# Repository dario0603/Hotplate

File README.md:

# Hotplate

**An open-source hotplate project for electronics and PCB work.**

> **Work in Progress** — This project is currently under development. Hardware designs, PCB revisions, documentation, and other project files may change.

## Overview

Hotplate is a DIY electronics project focused on the design and development of a hotplate and its associated control electronics.

This repository is intended to collect the hardware designs, PCB documentation, and project resources as development progresses.

## PCB Designs

### Hotplate Resistor

The custom PCB designed for the hotplate heating element.

### Hotplate Control Board v1.1

The control electronics PCB, revision v1.1.

## Repository Structure

```text
Hotplate/
├── img/
│   ├── hotplate-control-board-v1.1.png
│   └── hotplate-resistor.png
├── Kicad/
│   ├── Control board/
│   │   ├── Control board v1.0/
│   │   ├── Control board v1.1/
│   │   └── Control board v1.2/
│   ├── Resistor 10x10/
│   └── Resistor 15x15/
├── Program/
│   ├── lib/
│   ├── Master/
│   ├── Master_prova/
│   ├── backup1/
│   └── backup 2/
├── Simulation and circuits/
└── README.md
```

This tree shows the main project directories. Individual KiCad libraries, 3D models, backup files, and simulation outputs are omitted for readability

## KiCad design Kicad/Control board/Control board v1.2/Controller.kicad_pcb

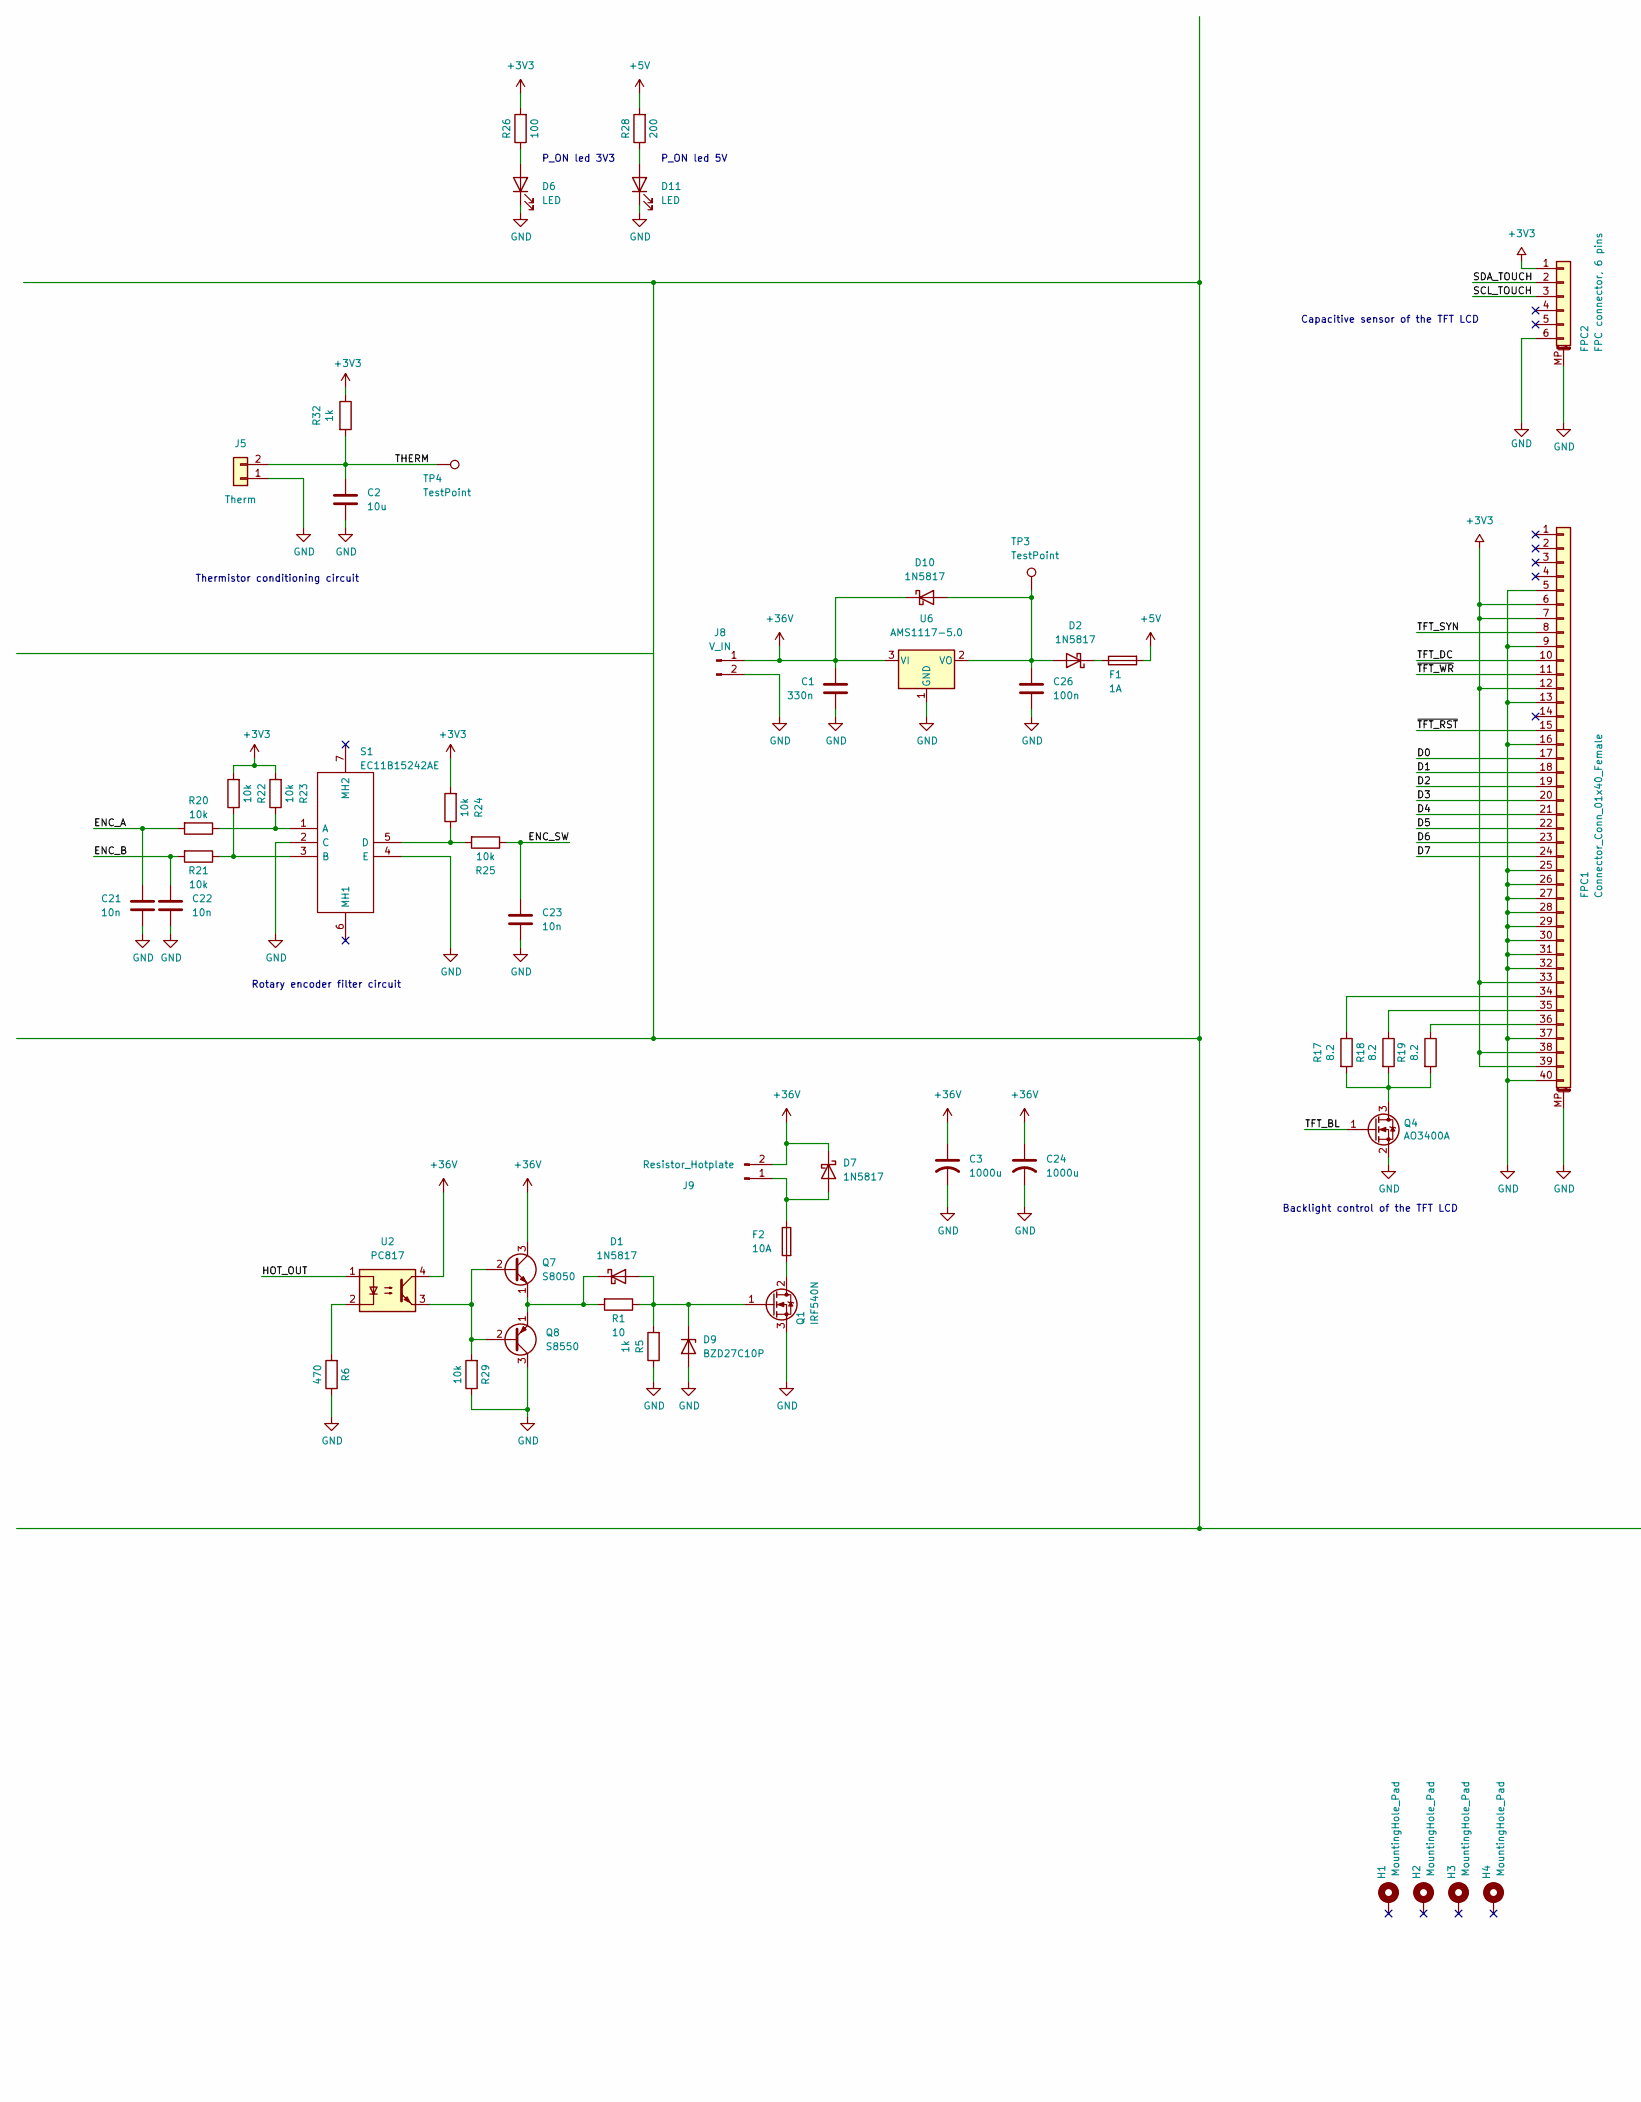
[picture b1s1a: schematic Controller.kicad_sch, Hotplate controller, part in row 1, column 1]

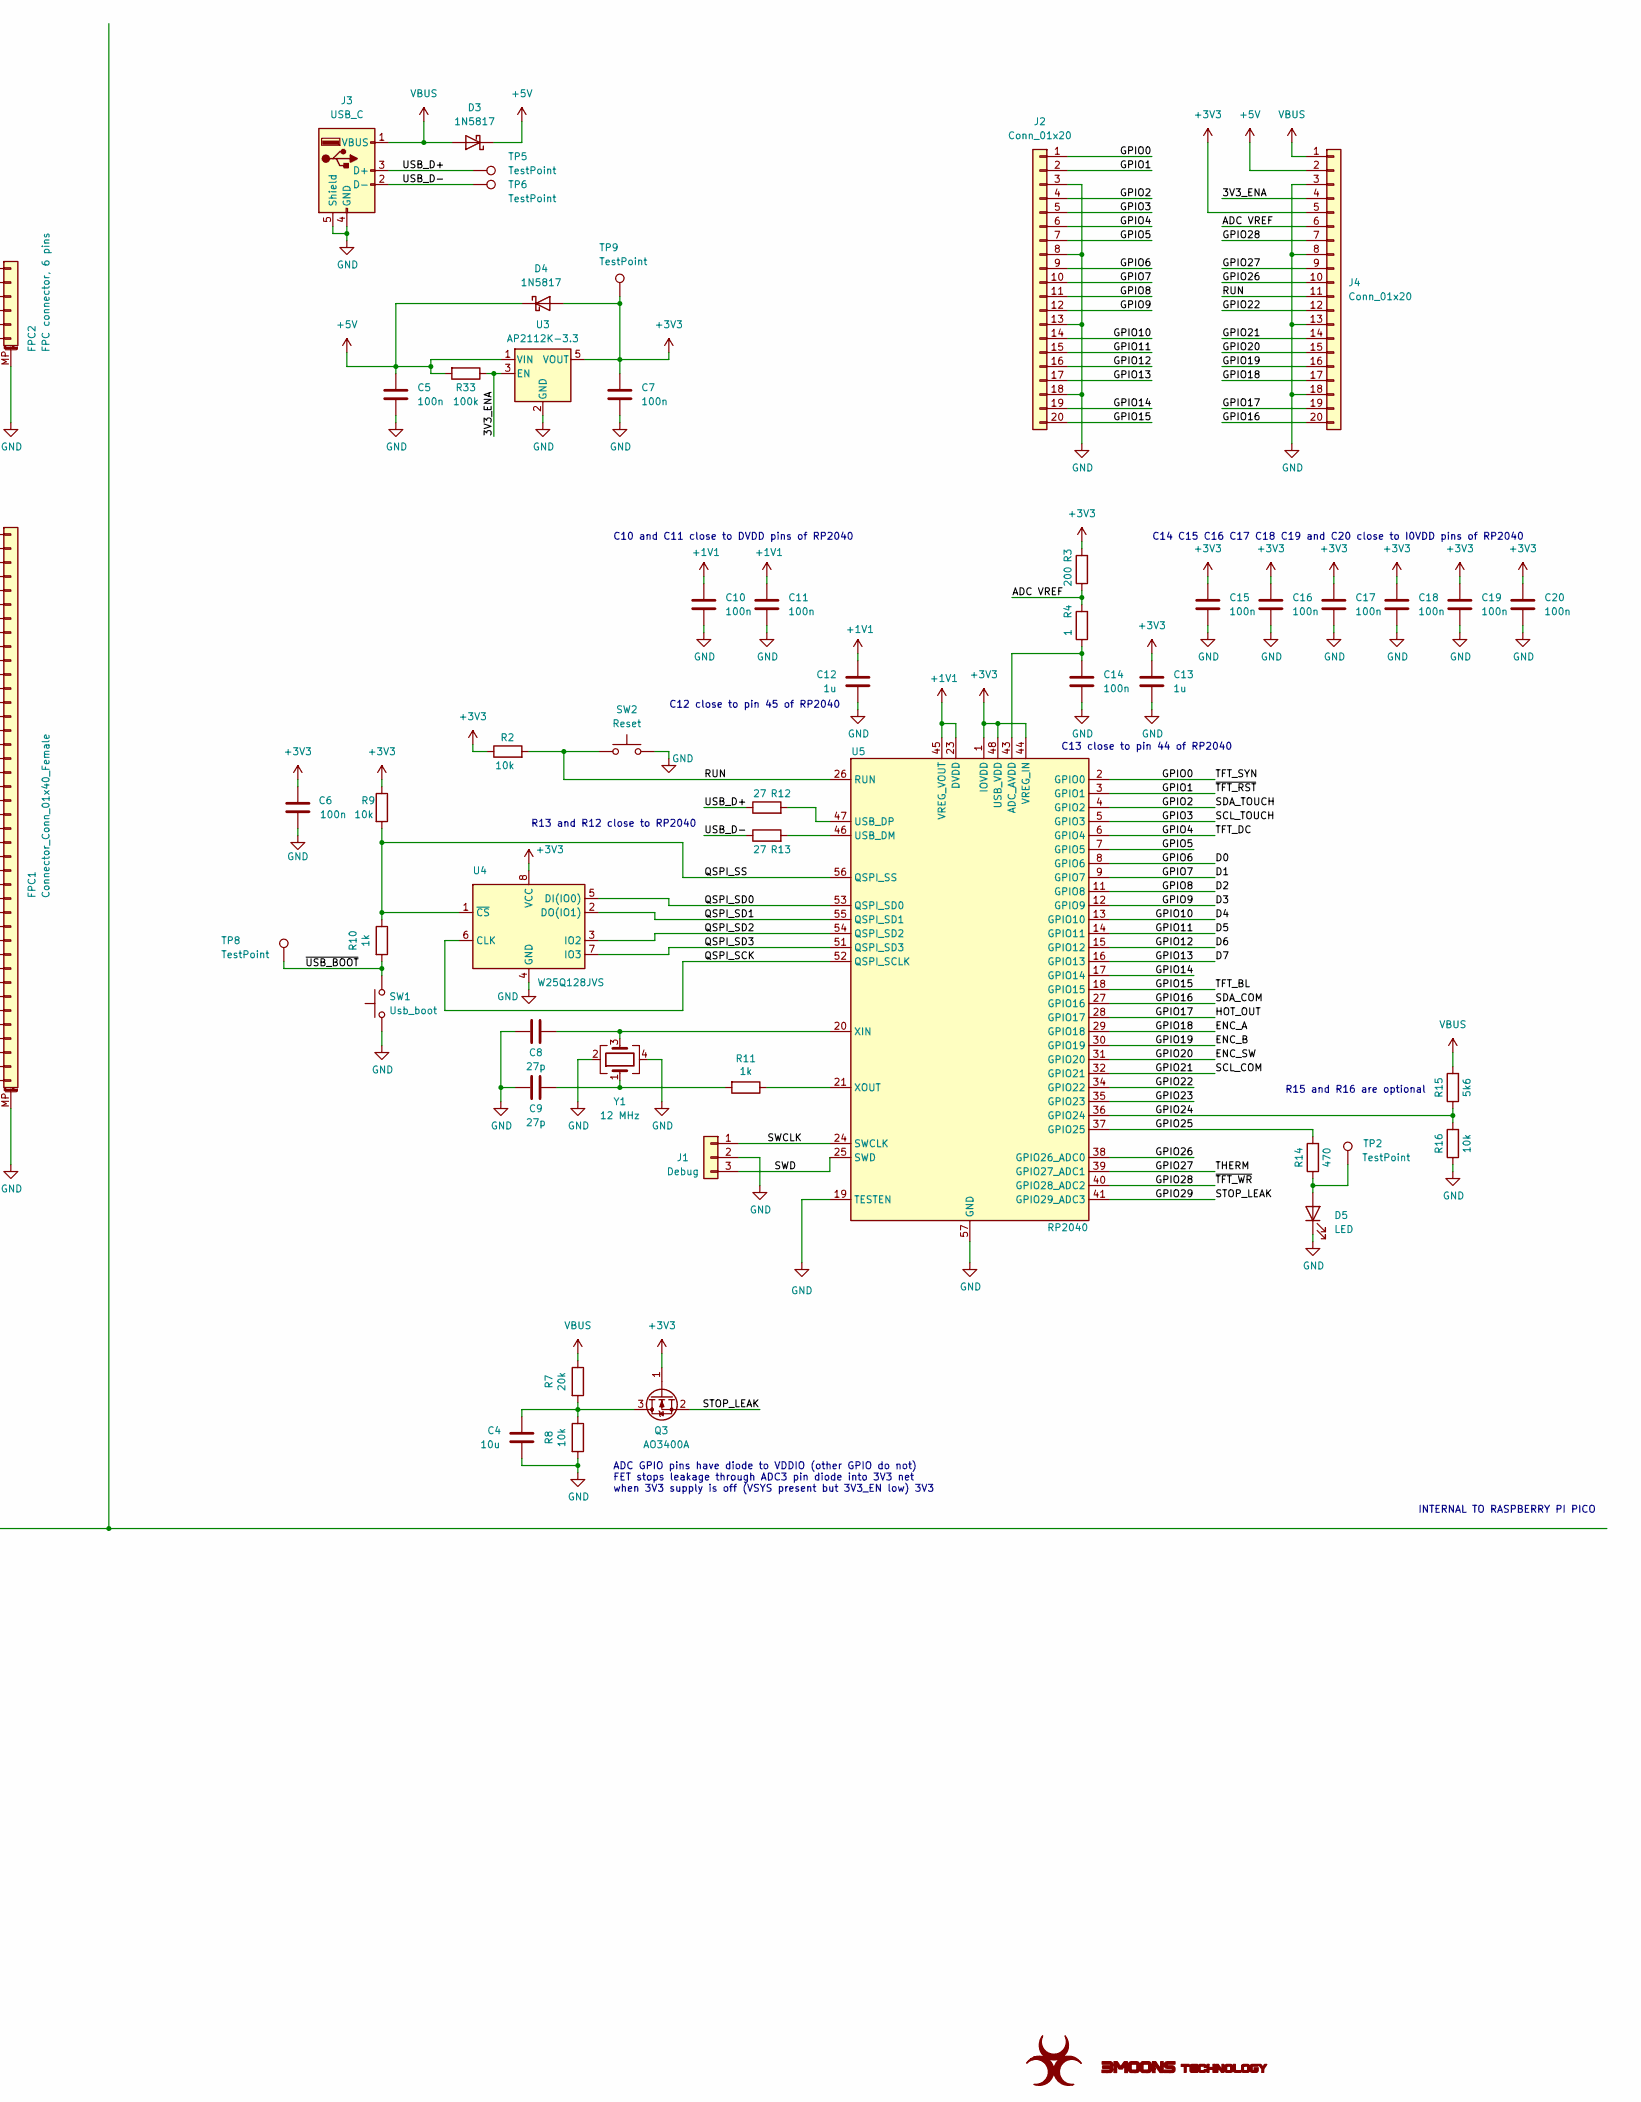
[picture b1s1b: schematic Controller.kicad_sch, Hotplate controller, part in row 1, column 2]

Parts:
C1: 330n; C_0805_2012Metric
C2: 10u; C_0805_2012Metric
C3, C24: 1000u; CP_Radial_D13.0mm_P5.00mm
C4: 10u; C_0402_1005Metric_Pad0.74x0.62mm_HandSolder
C5, C6, C7, C10, C11, C14, C15, C16, C17, C18, C19, C20: 100n; C_0402_1005Metric_Pad0.74x0.62mm_HandSolder
C8, C9: 27p; C_0402_1005Metric_Pad0.74x0.62mm_HandSolder
C12, C13: 1u; C_0402_1005Metric_Pad0.74x0.62mm_HandSolder
C21, C22, C23: 10n; C_0805_2012Metric
C26: 100n; C_0805_2012Metric
D1, D2, D7, D10: 1N5817; D_SMA
D3, D4: 1N5817; D_SOD-323_HandSoldering
D5, D6, D11: LED; LED_0805_2012Metric_Pad1.15x1.40mm_HandSolder
D9: BZD27C10P; D_SMF
F1: 1A; 0154.250DR
F2: 10A; Fuseholder_Cylinder-5x20mm_Schurter_0031_8201_Horizontal_Op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
FPC1: Connector_Conn_01x40_Female; Hirose_FH12-40S-0.5SH_1x40-1MP_P0.50mm_Horizontal
FPC2: FPC connector, 6 pins; Hirose_FH12-6S-0.5SH_1x06-1MP_P0.50mm_Horizontal
H1, H2, H3, H4: MountingHole_Pad; MountingHole_2.7mm_M2.5_DIN965_Pad
J1: Debug; 2.54mm pin 1x3
J2, J4: Conn_01x20; 2.54mm pin 1x20
J3: USB_C; USB_C_4_pin
J5: Therm; Molex_KK-254_AE-6410-02A_1x02_P2.54mm_Vertical
J8: V_IN; MK1000_P10mm_1x02
J9: Resistor_Hotplate; MK1000_P10mm_1x02
Q1: IRF540N; TO-220-3_Vertical
Q3, Q4: AO3400A; SOT-23; LCSC C20917
Q7: S8050; SOT-23
Q8: S8550; SOT-23
R1: 10; R_0805_2012Metric_Pad1.20x1.40mm_HandSolder
R2, R8, R9, R16: 10k; R_0402_1005Metric_Pad0.72x0.64mm_HandSolder
R3: 200; R_0402_1005Metric_Pad0.72x0.64mm_HandSolder
R4: 1; R_0402_1005Metric_Pad0.72x0.64mm_HandSolder
R5, R32: 1k; R_0805_2012Metric_Pad1.20x1.40mm_HandSolder
R6: 470; R_0805_2012Metric_Pad1.20x1.40mm_HandSolder
R7: 20k; R_0402_1005Metric_Pad0.72x0.64mm_HandSolder
R10, R11: 1k; R_0402_1005Metric_Pad0.72x0.64mm_HandSolder
R12, R13: 27; R_0402_1005Metric_Pad0.72x0.64mm_HandSolder
R14: 470; R_0402_1005Metric_Pad0.72x0.64mm_HandSolder
R15: 5k6; R_0402_1005Metric_Pad0.72x0.64mm_HandSolder
R17, R18, R19: 8.2; R_0805_2012Metric_Pad1.20x1.40mm_HandSolder
R20, R21, R22, R23, R24, R25, R29: 10k; R_0805_2012Metric_Pad1.20x1.40mm_HandSolder
R26: 100; R_0805_2012Metric_Pad1.20x1.40mm_HandSolder
R28: 200; R_0805_2012Metric_Pad1.20x1.40mm_HandSolder
R33: 100k; R_0402_1005Metric_Pad0.72x0.64mm_HandSolder
S1: EC11B15242AE; Manufacturer_Part_Number EC11B15242AE; Mouser Part Number 688-EC11B15242AE
SW1: Usb_boot; SW_SPST_B3U-1000P
SW2: Reset; SW_SPST_B3U-1000P
TP2, TP4, TP5, TP6, TP8: TestPoint; TestPoint_Pad_D1.0mm
TP3, TP9: TestPoint; TestPoint_Pad_D2.5mm
U2: PC817; DIP-4_W7.62mm
U3: AP2112K-3.3; SOT-23-5
U4: W25Q128JVS; SOIC-8_5.23x5.23mm_P1.27mm
U5: RP2040; RP2040-QFN-56
U6: AMS1117-5.0; SOT-223-3_TabPin2
Y1: 12 MHz; Crystal_SMD_7050-4Pin_7.0x5.0mm

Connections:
+1V1: C10.1, C11.1, C12.1, U5.23 (DVDD), U5.45 (VREG_VOUT), U5.50 (DVDD)
+3V3: C6.1, C7.1, C13.1, C15.1, C16.1, C17.1, C18.1, C19.1, C20.1, D4.2 (A), FPC1.6, FPC1.7, FPC1.12, FPC1.33, FPC1.38, FPC1.39, FPC2.1, J4.5, Q3.1 (G), R2.1, R3.2, R9.1, R22.2, R23.2, R24.2, R26.2, R32.1, TP9.1, U3.5 (VOUT), U4.8 (VCC), U5.1 (IOVDD), U5.10 (IOVDD), U5.22 (IOVDD), U5.33 (IOVDD), U5.42 (IOVDD), U5.44 (VREG_IN), U5.48 (USB_VDD), U5.49 (IOVDD)
+5V: C5.1, D3.1 (K), D4.1 (K), F1.2, J4.2, R28.2, R33.2, U3.1 (VIN)
+36V: C1.1, C3.1, C24.1, D7.1 (K), D10.1 (K), J8.1, J9.2, Q7.3 (C), U2.4, U6.3 (VI)
/3V3_ENA: J4.4, R33.1, U3.3 (EN)
/ADC VREF: J4.6, R3.1, R4.2
/D0: FPC1.17, J2.9, U5.8 (GPIO6)
/D1: FPC1.18, J2.10, U5.9 (GPIO7)
/D2: FPC1.19, J2.11, U5.11 (GPIO8)
/D3: FPC1.20, J2.12, U5.12 (GPIO9)
/D4: FPC1.21, J2.14, U5.13 (GPIO10)
/D5: FPC1.22, J2.15, U5.14 (GPIO11)
/D6: FPC1.23, J2.16, U5.15 (GPIO12)
/D7: FPC1.24, J2.17, U5.16 (GPIO13)
/ENC_A: C21.1, J4.17, R20.2, U5.29 (GPIO18)
/ENC_B: C22.1, J4.16, R21.2, U5.30 (GPIO19)
/ENC_SW: C23.1, J4.15, R25.1, U5.31 (GPIO20)
/GPIO0: FPC1.8, J2.1, U5.2 (GPIO0)
/GPIO1: FPC1.15, J2.2, U5.3 (GPIO1)
/GPIO2: FPC2.2, J2.4, U5.4 (GPIO2)
/GPIO3: FPC2.3, J2.5, U5.5 (GPIO3)
/GPIO4: FPC1.10, J2.6, U5.6 (GPIO4)
/GPIO5: J2.7, U5.7 (GPIO5)
/GPIO14: J2.19, U5.17 (GPIO14)
/GPIO15: J2.20, Q4.1 (G), U5.18 (GPIO15)
/GPIO16: J4.20, U5.27 (GPIO16)
/GPIO17: J4.19, U2.1, U5.28 (GPIO17)
/GPIO21: J4.14, U5.32 (GPIO21)
/GPIO22: J4.12, U5.34 (GPIO22)
/GPIO23: U5.35 (GPIO23)
/GPIO24: R15.1, R16.2, U5.36 (GPIO24)
/GPIO25: R14.2, U5.37 (GPIO25)
/GPIO26: J4.10, U5.38 (GPIO26_ADC0)
/GPIO27: C2.1, J4.9, J5.2, R32.2, TP4.1, U5.39 (GPIO27_ADC1)
/GPIO28: FPC1.11, J4.7, U5.40 (GPIO28_ADC2)
/GPIO29: Q3.2 (S), U5.41 (GPIO29_ADC3)
/QSPI_SCK: U4.6 (CLK), U5.52 (QSPI_SCLK)
/QSPI_SD0: U4.5 (DI(IO0)), U5.53 (QSPI_SD0)
/QSPI_SD1: U4.2 (DO(IO1)), U5.55 (QSPI_SD1)
/QSPI_SD2: U4.3 (IO2), U5.54 (QSPI_SD2)
/QSPI_SD3: U4.7 (IO3), U5.51 (QSPI_SD3)
/QSPI_SS: R9.2, R10.1, U4.1 (~CS), U5.56 (QSPI_SS)
/RUN: J4.11, R2.2, SW2.1, U5.26 (RUN)
/SWCLK: J1.1, U5.24 (SWCLK)
/SWD: J1.3, U5.25 (SWD)
/USB_D+: J3.3 (D+), R12.1, TP5.1
/USB_D-: J3.2 (D-), R13.1, TP6.1
/~USB_BOOT: R10.2, SW1.2, TP8.1
GND: C1.2, C2.2, C3.2, C4.2, C5.2, C6.2, C7.2, C8.1, C9.1, C10.2, C11.2, C12.2, C13.2, C14.2, C15.2, C16.2, C17.2, C18.2, C19.2, C20.2, C21.2, C22.2, C23.2, C24.2, C26.2, D5.1 (K), D6.1 (K), D9.2 (A), D11.1 (K), FPC1.5, FPC1.9, FPC1.13, FPC1.16, FPC1.25, FPC1.26, FPC1.27, FPC1.28, FPC1.29, FPC1.30, FPC1.31, FPC1.32, FPC1.37, FPC1.40, FPC1.MP (MountPin), FPC2.6, FPC2.MP (MountPin), J1.2, J2.3, J2.8, J2.13, J2.18, J3.4 (GND), J3.5 (Shield), J4.3, J4.8, J4.13, J4.18, J5.1, J8.2, Q1.3 (S), Q4.2 (S), Q8.3 (C), R5.1, R6.1, R8.2, R16.1, R29.1, S1.2 (C), S1.4 (E), SW1.1, SW2.2, U3.2 (GND), U4.4 (GND), U5.19 (TESTEN), U5.57 (GND), U6.1 (GND), Y1.2, Y1.4
unnamed: C9.2, R11.2, Y1.1
unnamed: D1.2 (A), D9.1 (K), Q1.1 (G), R1.1, R5.2
unnamed: D1.1 (K), Q7.1 (E), Q8.1 (E), R1.2
unnamed: D2.1 (K), F1.1
unnamed: D5.2 (A), R14.1, TP2.1
unnamed: D6.2 (A), R26.1
unnamed: D7.2 (A), F2.1, J9.1
unnamed: C26.1, D2.2 (A), D10.2 (A), TP3.1, U6.2 (VO)
unnamed: D11.2 (A), R28.1
unnamed: FPC1.34, R17.1
unnamed: FPC1.35, R18.1
unnamed: FPC1.36, R19.1
unnamed: F2.2, Q1.2 (D)
unnamed: C4.1, Q3.3 (D), R7.2, R8.1
unnamed: Q4.3 (D), R17.2, R18.2, R19.2
unnamed: Q7.2 (B), Q8.2 (B), R29.2, U2.3
unnamed: R6.2, U2.2
unnamed: R20.1, R23.1, S1.1 (A)
unnamed: R21.1, R22.1, S1.3 (B)
unnamed: R24.1, R25.2, S1.5 (D)
unnamed: C14.1, R4.1, U5.43 (ADC_AVDD)
unnamed: R13.2, U5.46 (USB_DM)
unnamed: R12.2, U5.47 (USB_DP)
unnamed: C8.2, U5.20 (XIN), Y1.3
unnamed: R11.1, U5.21 (XOUT)
VBUS: D3.2 (A), J3.1 (VBUS), J4.1, R7.1, R15.2

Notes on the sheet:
Backlight control of the TFT LCD
ADC GPIO pins have diode to VDDIO (other GPIO do not) FET stops leakage through ADC3 pin diode into 3V3 net when 3V3 supply is off (VSYS present but 3V3_EN low) 3V3
C14 C15 C16 C17 C18 C19 and C20 close to I0VDD pins of RP2040
C10 and C11 close to DVDD pins of RP2040
P_ON led 3V3
P_ON led 5V
C12 close to pin 45 of RP2040
R15 and R16 are optional
R13 and R12 close to RP2040
Capacitive sensor of the TFT LCD
Rotary encoder filter circuit
Thermistor conditioning circuit
INTERNAL TO RASPBERRY PI PICO
C13 close to pin 44 of RP2040

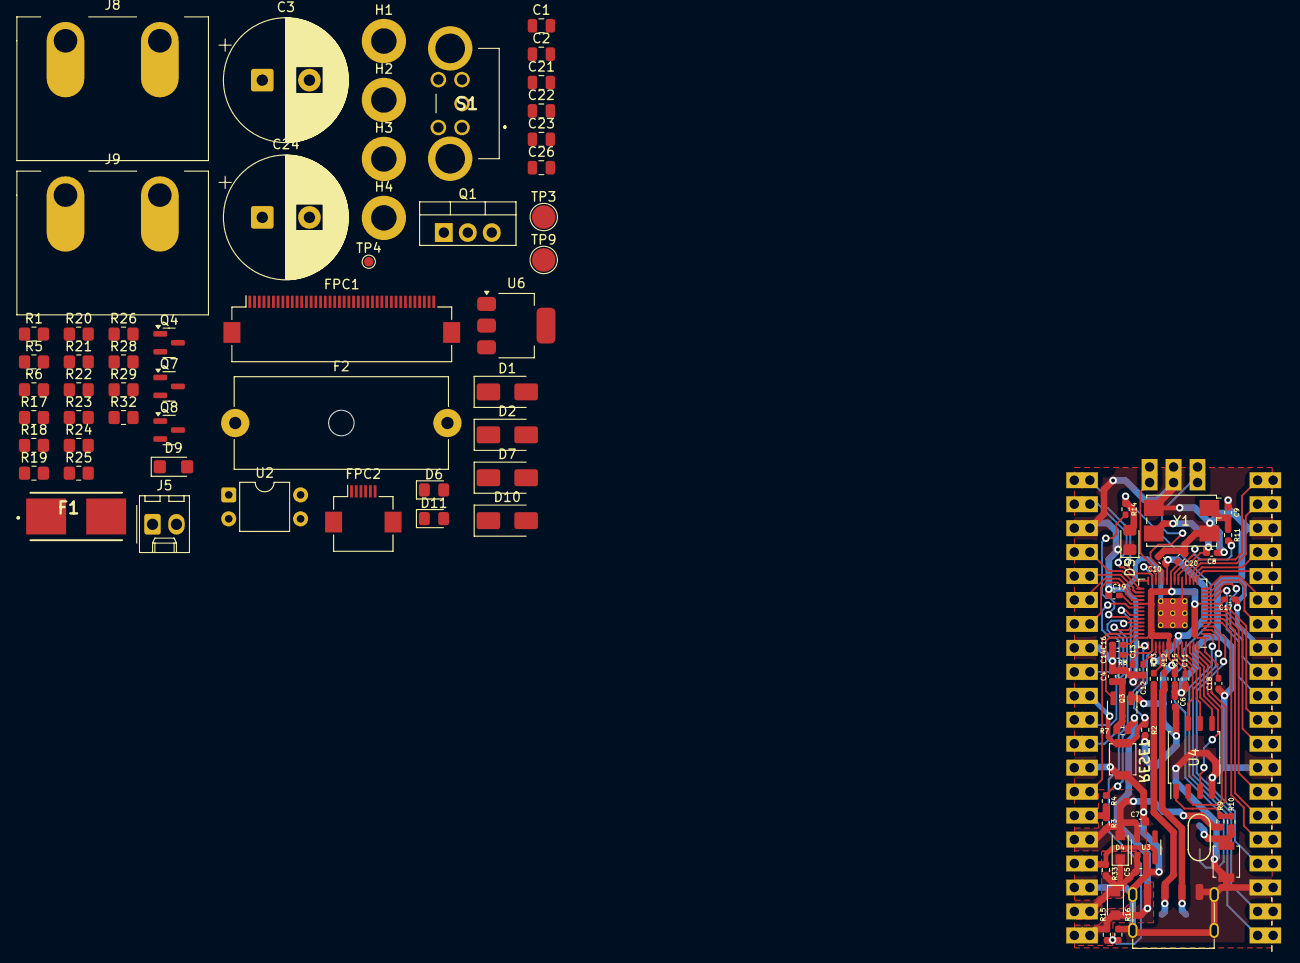
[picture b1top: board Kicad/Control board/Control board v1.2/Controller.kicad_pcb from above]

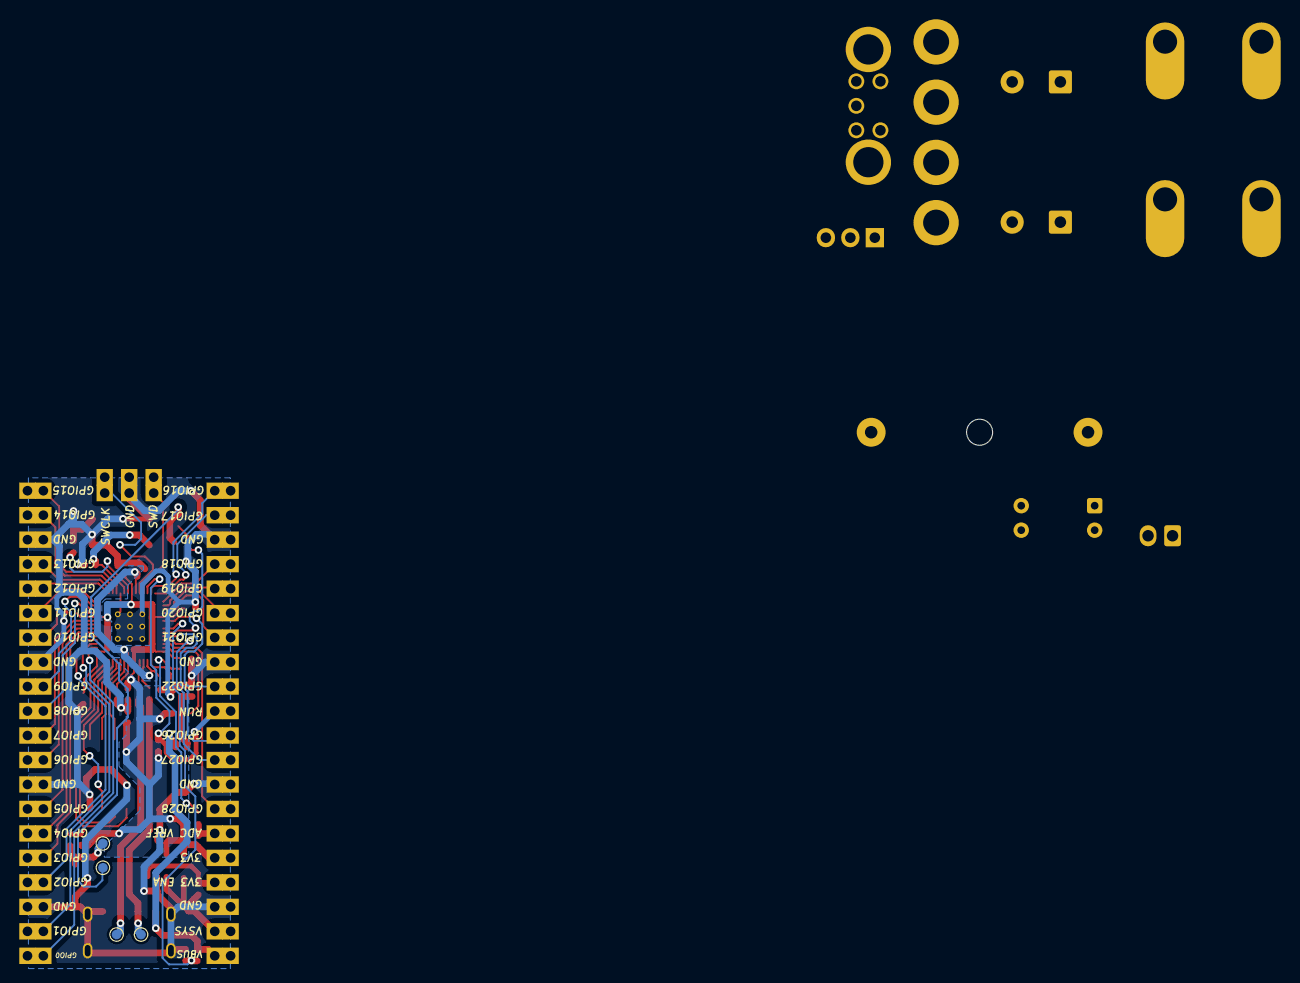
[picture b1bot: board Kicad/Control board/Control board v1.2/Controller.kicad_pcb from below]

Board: 2 copper layers, 101 parts (4 on the bottom side), 74 nets.

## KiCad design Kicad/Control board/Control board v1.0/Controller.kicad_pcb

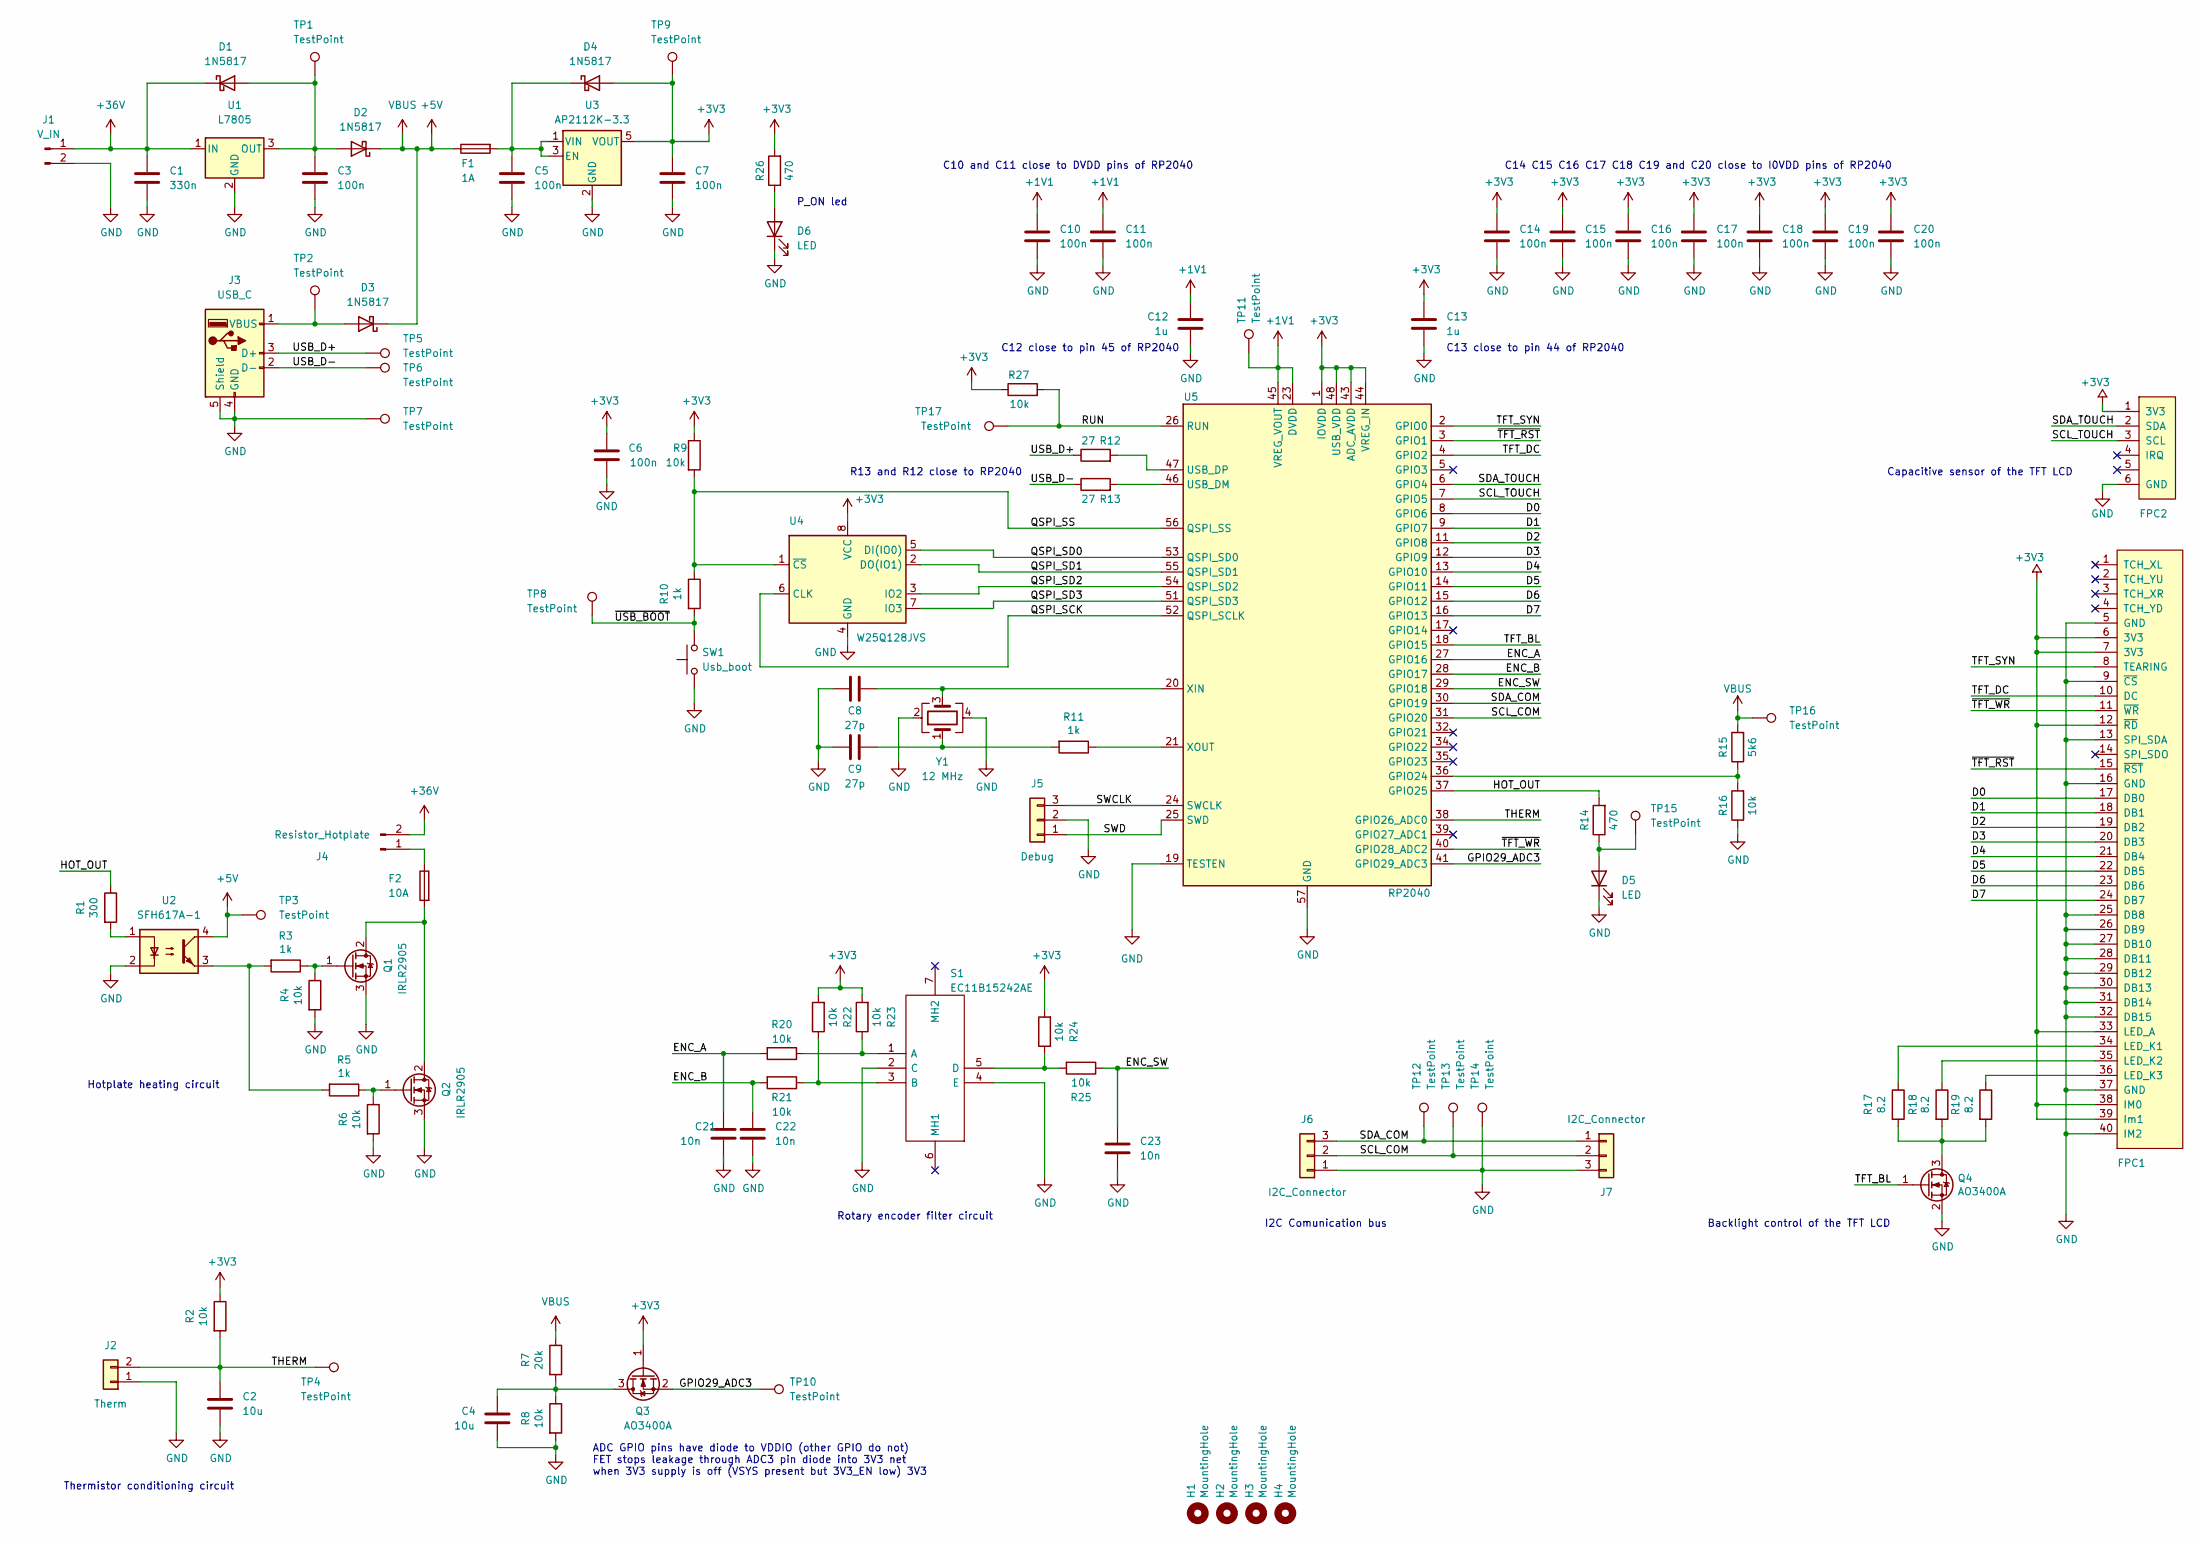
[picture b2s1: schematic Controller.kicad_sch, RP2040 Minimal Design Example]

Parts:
C1: 330n; C_0805_2012Metric
C2, C4: 10u; C_0805_2012Metric
C3, C5, C6, C7, C10, C11, C14, C15, C16, C17, C18, C19, C20: 100n; C_0805_2012Metric
C8, C9: 27p; C_0805_2012Metric
C12, C13: 1u; C_0805_2012Metric
C21, C22, C23: 10n; C_0805_2012Metric
D1, D2, D3, D4: 1N5817; D_SMA
D5, D6: LED; LED_0805_2012Metric_Pad1.15x1.40mm_HandSolder
F1: 1A; 0154.250DR
F2: 10A; Fuseholder_Cylinder-5x20mm_Schurter_0031_8201_Horizontal_Op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
FPC1: Connector_Conn_01x40_Female; Hirose_FH12-40S-0.5SH_1x40-1MP_P0.50mm_Horizontal; LCSC C11097
FPC2: FPC connector, 6 pins, 0.5mm, BOTTOM contacts; Hirose_FH12-6S-0.5SH_1x06-1MP_P0.50mm_Horizontal; LCSC C262262
H1, H2, H3, H4: MountingHole; MountingHole_2.7mm_M2.5_DIN965_Pad
J1: V_IN; MK1000_P10mm_1x02
J2: Therm; Molex_KK-254_AE-6410-02A_1x02_P2.54mm_Vertical
J3: USB_C; USB_C_4_pin
J4: Resistor_Hotplate; MK1000_P10mm_1x02
J5: Debug; PinHeader_1x03_P2.54mm_Vertical
J6, J7: I2C_Connector; JST_XH_S3B-XH-A-1_1x03_P2.50mm_Horizontal
Q1, Q2: IRLR2905; TO-252-2
Q3, Q4: AO3400A; SOT-23; LCSC C20917
R1: 300; R_0805_2012Metric_Pad1.20x1.40mm_HandSolder
R2, R4, R6, R8, R9, R16, R20, R21, R22, R23, R24, R25, R27: 10k; R_0805_2012Metric_Pad1.20x1.40mm_HandSolder
R3, R5, R10, R11: 1k; R_0805_2012Metric_Pad1.20x1.40mm_HandSolder
R7: 20k; R_0805_2012Metric_Pad1.20x1.40mm_HandSolder
R12, R13: 27; R_0805_2012Metric_Pad1.20x1.40mm_HandSolder
R14, R26: 470; R_0805_2012Metric_Pad1.20x1.40mm_HandSolder
R15: 5k6; R_0805_2012Metric_Pad1.20x1.40mm_HandSolder
R17, R18, R19: 8.2; R_0805_2012Metric_Pad1.20x1.40mm_HandSolder
S1: EC11B15242AE; Manufacturer_Part_Number EC11B15242AE; Mouser Part Number 688-EC11B15242AE
SW1: Usb_boot; SW_SPST_B3S-1000
TP1, TP2, TP3, TP7, TP9: TestPoint; TestPoint_Pad_D2.5mm
TP4, TP5, TP6, TP8, TP10, TP11, TP12, TP13, TP14, TP15, TP16, TP17: TestPoint; TestPoint_Pad_D1.0mm
U1: L7805; TO-252-3_TabPin2
U2: SFH617A-1; DIP-4_W7.62mm
U3: AP2112K-3.3; SOT-23-5
U4: W25Q128JVS; SOIC-8_5.23x5.23mm_P1.27mm
U5: RP2040; RP2040-QFN-56
Y1: 12 MHz; Crystal_SMD_7050-4Pin_7.0x5.0mm

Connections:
+1V1: C10.1, C11.1, C12.1, TP11.1, U5.23 (DVDD), U5.45 (VREG_VOUT), U5.50 (DVDD)
+3V3: C6.1, C7.1, C13.1, C14.1, C15.1, C16.1, C17.1, C18.1, C19.1, C20.1, D4.2 (A), FPC1.6 (3V3), FPC1.7 (3V3), FPC1.12 (~RD), FPC1.33 (LED_A), FPC1.38 (IM0), FPC1.39 (Im1), FPC2.1 (3V3), Q3.1 (G), R2.1, R9.1, R22.2, R23.2, R24.2, R26.2, R27.1, TP9.1, U3.5 (VOUT), U4.8 (VCC), U5.1 (IOVDD), U5.10 (IOVDD), U5.22 (IOVDD), U5.33 (IOVDD), U5.42 (IOVDD), U5.43 (ADC_AVDD), U5.44 (VREG_IN), U5.48 (USB_VDD), U5.49 (IOVDD)
+5V: D2.1 (K), D3.1 (K), F1.1, R7.1, R15.2, TP3.1, TP16.1, U2.4
+36V: C1.1, D1.1 (K), J1.1, J4.2, U1.1 (IN)
/D0: FPC1.17 (DB0), U5.8 (GPIO6)
/D1: FPC1.18 (DB1), U5.9 (GPIO7)
/D2: FPC1.19 (DB2), U5.11 (GPIO8)
/D3: FPC1.20 (DB3), U5.12 (GPIO9)
/D4: FPC1.21 (DB4), U5.13 (GPIO10)
/D5: FPC1.22 (DB5), U5.14 (GPIO11)
/D6: FPC1.23 (DB6), U5.15 (GPIO12)
/D7: FPC1.24 (DB7), U5.16 (GPIO13)
/ENC_A: C21.1, R20.2, U5.27 (GPIO16)
/ENC_B: C22.1, R21.2, U5.28 (GPIO17)
/ENC_SW: C23.1, R25.1, U5.29 (GPIO18)
/GPIO29_ADC3: Q3.2 (S), TP10.1, U5.41 (GPIO29_ADC3)
/HOT_OUT: R1.1, R14.2, U5.37 (GPIO25)
/QSPI_SCK: U4.6 (CLK), U5.52 (QSPI_SCLK)
/QSPI_SD0: U4.5 (DI(IO0)), U5.53 (QSPI_SD0)
/QSPI_SD1: U4.2 (DO(IO1)), U5.55 (QSPI_SD1)
/QSPI_SD2: U4.3 (IO2), U5.54 (QSPI_SD2)
/QSPI_SD3: U4.7 (IO3), U5.51 (QSPI_SD3)
/QSPI_SS: R9.2, R10.1, U4.1 (~CS), U5.56 (QSPI_SS)
/RUN: R27.2, TP17.1, U5.26 (RUN)
/SCL_COM: J6.2, J7.2, TP13.1, U5.31 (GPIO20)
/SCL_TOUCH: FPC2.3 (SCL), U5.7 (GPIO5)
/SDA_COM: J6.3, J7.1, TP12.1, U5.30 (GPIO19)
/SDA_TOUCH: FPC2.2 (SDA), U5.6 (GPIO4)
/SWCLK: J5.3, U5.24 (SWCLK)
/SWD: J5.1, U5.25 (SWD)
/TFT_BL: Q4.1 (G), U5.18 (GPIO15)
/TFT_DC: FPC1.10 (DC), U5.4 (GPIO2)
/TFT_SYN: FPC1.8 (TEARING), U5.2 (GPIO0)
/THERM: C2.1, J2.2, R2.2, TP4.1, U5.38 (GPIO26_ADC0)
/USB_D+: J3.3 (D+), R12.1, TP5.1
/USB_D-: J3.2 (D-), R13.1, TP6.1
/~TFT_RST: FPC1.15 (~RST), U5.3 (GPIO1)
/~TFT_WR: FPC1.11 (~WR), U5.40 (GPIO28_ADC2)
/~USB_BOOT: R10.2, SW1.2, TP8.1
GND: C1.2, C2.2, C3.2, C4.2, C5.2, C6.2, C7.2, C8.1, C9.1, C10.2, C11.2, C12.2, C13.2, C14.2, C15.2, C16.2, C17.2, C18.2, C19.2, C20.2, C21.2, C22.2, C23.2, D5.1 (K), D6.1 (K), FPC1.5 (GND), FPC1.9 (~CS), FPC1.13 (SPI_SDA), FPC1.16 (GND), FPC1.25 (DB8), FPC1.26 (DB9), FPC1.27 (DB10), FPC1.28 (DB11), FPC1.29 (DB12), FPC1.30 (DB13), FPC1.31 (DB14), FPC1.32 (DB15), FPC1.37 (GND), FPC1.40 (IM2), FPC2.6 (GND), J1.2, J2.1, J3.4 (GND), J3.5 (Shield), J5.2, J6.1, J7.3, Q1.3 (S), Q2.3 (S), Q4.2 (S), R4.2, R6.2, R8.2, R16.1, S1.2 (C), S1.4 (E), SW1.1, TP7.1, TP14.1, U1.2 (GND), U2.2, U3.2 (GND), U4.4 (GND), U5.19 (TESTEN), U5.57 (GND), Y1.2, Y1.4
unnamed: C3.1, D1.2 (A), D2.2 (A), TP1.1, U1.3 (OUT)
unnamed: C4.1, Q3.3 (D), R7.2, R8.1
unnamed: C5.1, D4.1 (K), F1.2, U3.1 (VIN), U3.3 (EN)
unnamed: C8.2, U5.20 (XIN), Y1.3
unnamed: C9.2, R11.2, Y1.1
unnamed: D3.2 (A), J3.1 (VBUS), TP2.1
unnamed: D5.2 (A), R14.1, TP15.1
unnamed: D6.2 (A), R26.1
unnamed: F2.1, J4.1
unnamed: F2.2, Q1.2 (D), Q2.2 (D)
unnamed: FPC1.34 (LED_K1), R17.1
unnamed: FPC1.35 (LED_K2), R18.1
unnamed: FPC1.36 (LED_K3), R19.1
unnamed: Q1.1 (G), R3.1, R4.1
unnamed: Q2.1 (G), R5.1, R6.1
unnamed: Q4.3 (D), R17.2, R18.2, R19.2
unnamed: R1.2, U2.1
unnamed: R3.2, R5.2, U2.3
unnamed: R11.1, U5.21 (XOUT)
unnamed: R12.2, U5.47 (USB_DP)
unnamed: R13.2, U5.46 (USB_DM)
unnamed: R15.1, R16.2, U5.36 (GPIO24)
unnamed: R20.1, R23.1, S1.1 (A)
unnamed: R21.1, R22.1, S1.3 (B)
unnamed: R24.1, R25.2, S1.5 (D)

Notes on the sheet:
ADC GPIO pins have diode to VDDIO (other GPIO do not) FET stops leakage through ADC3 pin diode into 3V3 net when 3V3 supply is off (VSYS present but 3V3_EN low) 3V3
R13 and R12 close to RP2040
C14 C15 C16 C17 C18 C19 and C20 close to I0VDD pins of RP2040
Backlight control of the TFT LCD
I2C Comunication bus
C13 close to pin 44 of RP2040
C12 close to pin 45 of RP2040
P_ON led
Capacitive sensor of the TFT LCD
Hotplate heating circuit
Rotary encoder filter circuit
C10 and C11 close to DVDD pins of RP2040
Thermistor conditioning circuit

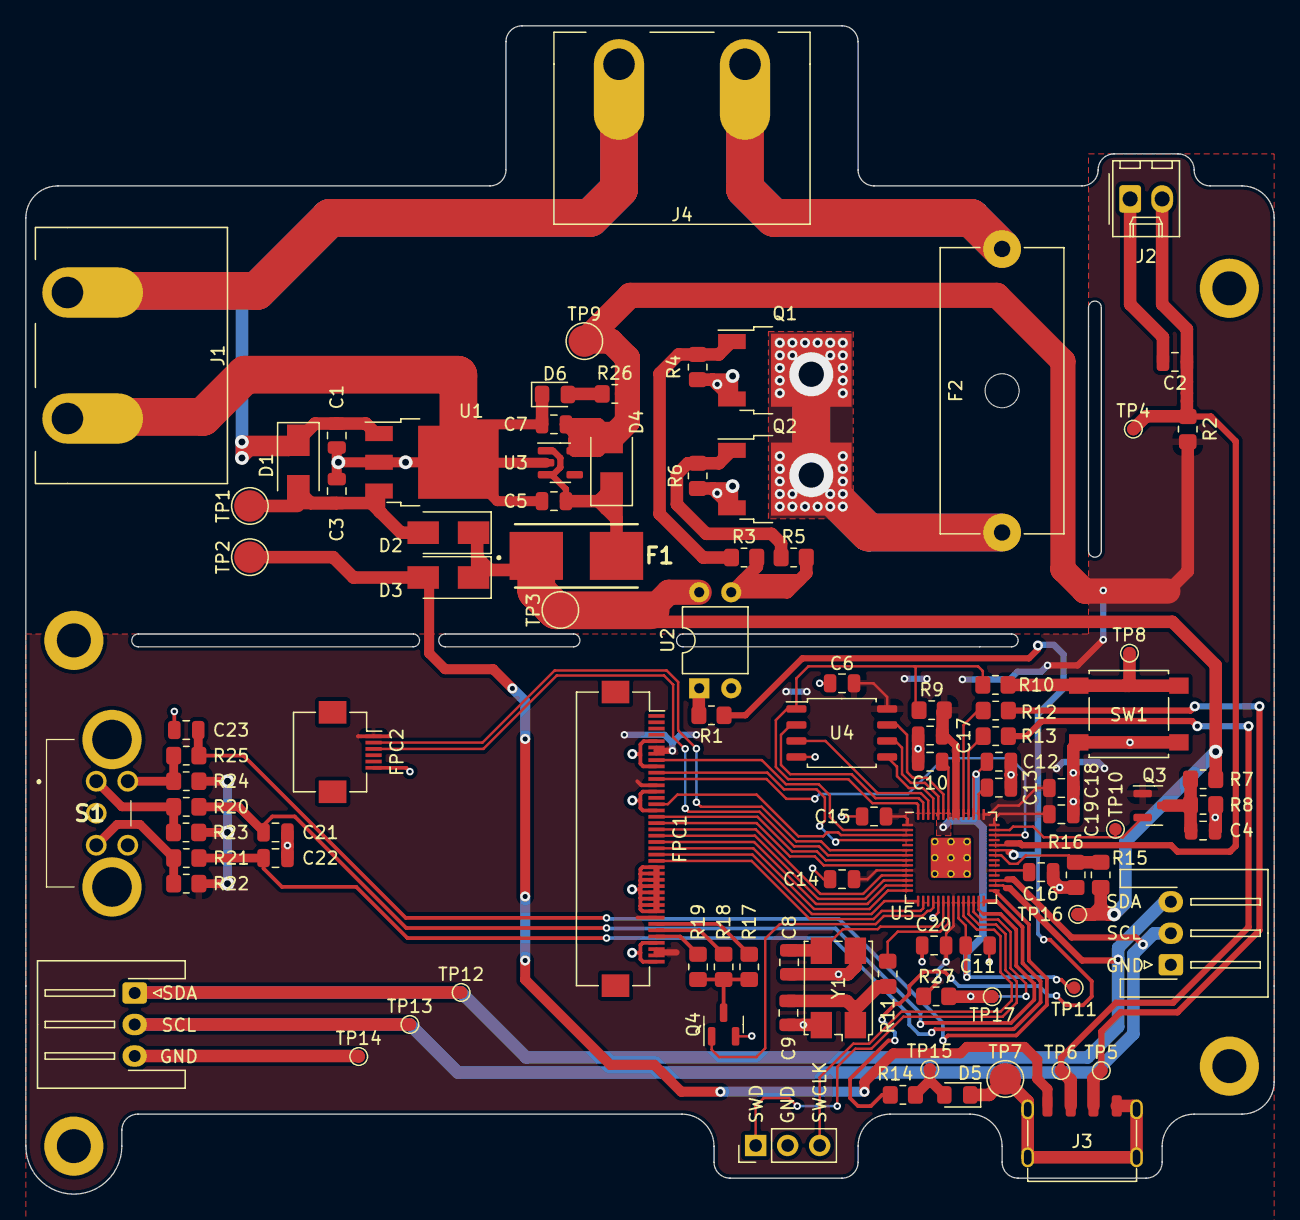
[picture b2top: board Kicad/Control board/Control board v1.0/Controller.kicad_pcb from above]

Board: 2 copper layers, 99.1 x 92.7 mm, 100 parts (0 on the bottom side), 65 nets.

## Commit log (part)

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2026-04-23 update 1
